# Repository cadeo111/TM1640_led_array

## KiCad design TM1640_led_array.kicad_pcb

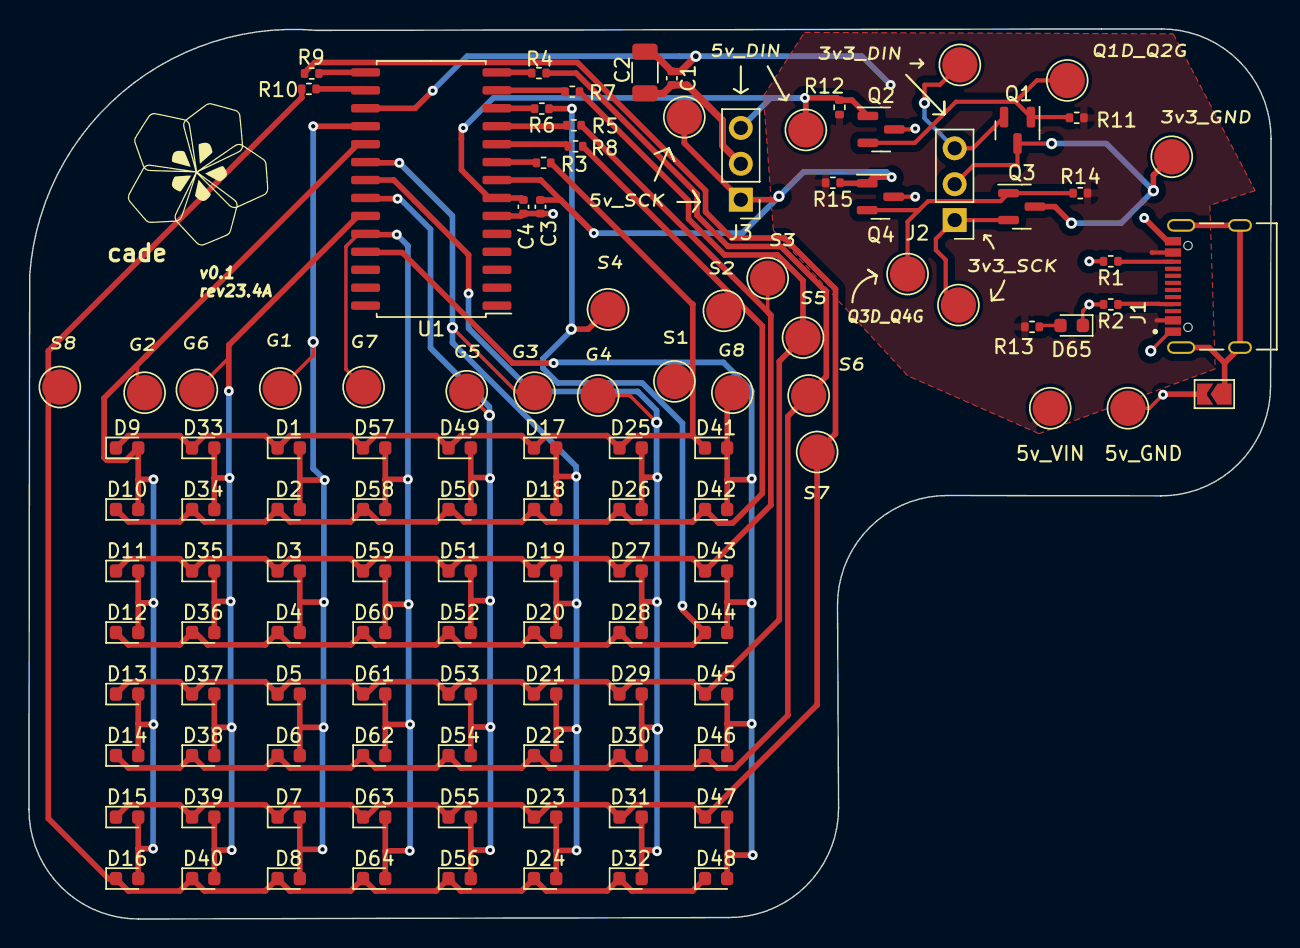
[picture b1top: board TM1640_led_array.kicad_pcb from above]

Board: 2 copper layers, 87.9 x 63.0 mm, 118 parts (0 on the bottom side), 37 nets.

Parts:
C1: 0.1uF; C_0402_1005Metric
C2: 100uF; C_1206_3216Metric
C3, C4: 100pf; C_0402_1005Metric
D1, D2, D3, D4, D5, D6, D7, D8, D9, D10, D11, D12, D13, D14, D15, D16, D17, D18, D19, D20, D21, D22, D23, D24, D25, D26, D27, D28, D29, D30, D31, D32, D33, D34, D35, D36, D37, D38, D39, D40, D41, D42, D43, D44, D45, D46, D47, D48, D49, D50, D51, D52, D53, D54, D55, D56, D57, D58, D59, D60, D61, D62, D63, D64: LED; LED_0603_1608Metric
D65: PWR_LED; LED_0603_1608Metric
J1: TYPE-C-31-M-12; HRO_TYPE-C-31-M-12
J2: 3v3_H; PinHeader_1x03_P2.54mm_Vertical
J3: 5v_H; PinHeader_1x03_P2.54mm_Vertical
JP1: SHEILD_GND; SolderJumper-2_P1.3mm_Open_TrianglePad1.0x1.5mm
Q1, Q2, Q3, Q4: NMOS; SOT-23
R1, R2, R11, R12, R13, R14, R15: 5k1; R_0402_1005Metric
R3, R4, R5, R6, R7, R8, R9, R10: 150R; R_0402_1005Metric
TP1: 3v3_DIN; TestPoint_Pad_D2.5mm
TP2: Q1D_Q2G; TestPoint_Pad_D2.5mm
TP3: 5v_DIN; TestPoint_Pad_D2.5mm
TP4: Q3D_Q4G; TestPoint_Pad_D2.5mm
TP5: 5v_SCK; TestPoint_Pad_D2.5mm
TP6: 3v3_SCK; TestPoint_Pad_D2.5mm
TP7: 3v3_GND; TestPoint_Pad_D2.5mm
TP8: G1; TestPoint_Pad_D2.5mm
TP9: G2; TestPoint_Pad_D2.5mm
TP10: G3; TestPoint_Pad_D2.5mm
TP11: G4; TestPoint_Pad_D2.5mm
TP12: G5; TestPoint_Pad_D2.5mm
TP13: G6; TestPoint_Pad_D2.5mm
TP14: G7; TestPoint_Pad_D2.5mm
TP15: G8; TestPoint_Pad_D2.5mm
TP16: S3; TestPoint_Pad_D2.5mm
TP17: S4; TestPoint_Pad_D2.5mm
TP18: S1; TestPoint_Pad_D2.5mm
TP19: S2; TestPoint_Pad_D2.5mm
TP20: S6; TestPoint_Pad_D2.5mm
TP21: S5; TestPoint_Pad_D2.5mm
TP22: S8; TestPoint_Pad_D2.5mm
TP23: S7; TestPoint_Pad_D2.5mm
TP24: 5v_VIN; TestPoint_Pad_D2.5mm
TP25: 5v_GND; TestPoint_Pad_D2.5mm
U1: SOIC-28W_7.5x17.9mm_P1.27mm

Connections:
/3V3_DIN: J2.3, Q1.2 (G), TP1.1
/3V3_SCK: J2.1, Q3.2 (G), TP6.1
/3v3_GND: J2.2, Q1.3 (S), Q3.3 (S), TP7.1
/5V_DIN: C4.1, J3.3, Q2.1 (D), R12.1, TP3.1, U1.7 (DIN)
/5V_SCK: C3.1, J3.1, Q4.1 (D), R15.1, TP5.1, U1.8 (SCLK)
/GRID1: D1.2 (A), D2.2 (A), D3.2 (A), D4.2 (A), D5.2 (A), D6.2 (A), D7.2 (A), D8.2 (A), TP8.1, U1.18 (GRID1)
/GRID2: D9.2 (A), D10.2 (A), D11.2 (A), D12.2 (A), D13.2 (A), D14.2 (A), D15.2 (A), D16.2 (A), TP9.1, U1.19 (GRID2)
/GRID3: D17.2 (A), D18.2 (A), D19.2 (A), D20.2 (A), D21.2 (A), D22.2 (A), D23.2 (A), D24.2 (A), TP10.1, U1.20 (GRID3)
/GRID4: D25.2 (A), D26.2 (A), D27.2 (A), D28.2 (A), D29.2 (A), D30.2 (A), D31.2 (A), D32.2 (A), TP11.1, U1.21 (GRID4)
/GRID5: D49.2 (A), D50.2 (A), D51.2 (A), D52.2 (A), D53.2 (A), D54.2 (A), D55.2 (A), D56.2 (A), TP12.1, U1.22 (GRID5)
/GRID6: D33.2 (A), D34.2 (A), D35.2 (A), D36.2 (A), D37.2 (A), D38.2 (A), D39.2 (A), D40.2 (A), TP13.1, U1.23 (GRID6)
/GRID7: D57.2 (A), D58.2 (A), D59.2 (A), D60.2 (A), D61.2 (A), D62.2 (A), D63.2 (A), D64.2 (A), TP14.1, U1.24 (GRID7)
/GRID8: D41.2 (A), D42.2 (A), D43.2 (A), D44.2 (A), D45.2 (A), D46.2 (A), D47.2 (A), D48.2 (A), TP15.1, U1.25 (GRID8)
/SEG1: D1.1 (K), D9.1 (K), D17.1 (K), D25.1 (K), D33.1 (K), D41.1 (K), D49.1 (K), D57.1 (K), R3.2, TP18.1
/SEG2: D2.1 (K), D10.1 (K), D18.1 (K), D26.1 (K), D34.1 (K), D42.1 (K), D50.1 (K), D58.1 (K), R8.1, TP19.1
/SEG3: D3.1 (K), D11.1 (K), D19.1 (K), D27.1 (K), D35.1 (K), D43.1 (K), D51.1 (K), D59.1 (K), R5.2, TP16.1
/SEG4: D4.1 (K), D12.1 (K), D20.1 (K), D28.1 (K), D36.1 (K), D44.1 (K), D52.1 (K), D60.1 (K), R6.1, TP17.1
/SEG5: D5.1 (K), D13.1 (K), D21.1 (K), D29.1 (K), D37.1 (K), D45.1 (K), D53.1 (K), D61.1 (K), R7.1, TP21.1
/SEG6: D6.1 (K), D14.1 (K), D22.1 (K), D30.1 (K), D38.1 (K), D46.1 (K), D54.1 (K), D62.1 (K), R4.1, TP20.1
/SEG7: D7.1 (K), D15.1 (K), D23.1 (K), D31.1 (K), D39.1 (K), D47.1 (K), D55.1 (K), D63.1 (K), R9.2, TP23.1
/SEG8: D8.1 (K), D16.1 (K), D24.1 (K), D32.1 (K), D40.1 (K), D48.1 (K), D56.1 (K), D64.1 (K), R10.1, TP22.1
GND: C1.2, C2.2, C3.2, C4.2, D65.1 (K), J1.A1_B12 (GND), J1.B1_A12 (GND), J3.2, JP1.2 (B), Q2.3 (S), Q4.3 (S), R1.2, R2.2, TP25.1, U1.6 (VSS)
unnamed: D65.2 (A), R13.1
unnamed: J1.A5 (CC1), R2.1
unnamed: J1.B5 (CC2), R1.1
unnamed: J1.S1 (SHIELD), J1.S2 (SHIELD), J1.S3 (SHIELD), J1.S4 (SHIELD), JP1.1 (A)
unnamed: Q1.1 (D), Q2.2 (G), R11.1, TP2.1
unnamed: Q3.1 (D), Q4.2 (G), R14.1, TP4.1
unnamed: R3.1, U1.9 (SEG1)
unnamed: R8.2, U1.10 (SEG2)
unnamed: R5.1, U1.11 (SEG3)
unnamed: R6.2, U1.12 (SEG4)
unnamed: R7.2, U1.13 (SEG5)
unnamed: R4.2, U1.14 (SEG6)
unnamed: R9.1, U1.15 (SEG7)
unnamed: R10.2, U1.16 (SEG8)
VBUS: C1.1, C2.1, J1.A4_B9 (VBUS), J1.B4_A9 (VBUS), R11.2, R12.2, R13.2, R14.2, R15.2, TP24.1, U1.17 (VDD)

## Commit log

2023-04-16 initial
2023-04-16 added filter caps for driver chip to schematic
2023-04-16 added filter caps to pcb layout
